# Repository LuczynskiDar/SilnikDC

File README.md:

# DC Engine driver ( Sterownik prędkości silnika DC )

> DC Engine driver is a [post graduate thesis](https://github.com/LuczynskiDar/SilnikDC/blob/master/Praca%20Podyplomowa%20-%20Sterownik%20Silnika%20-%20Dariusz%20%C5%81uczy%C5%84ski.pdf) done for AGH Univerisity of Science and Technology.

## Purpose of project

The purose of project was to use ECAD, EAGLE to design a circuit analog with
PCBA, then wirte a C program for Atmega32 to dirive a DC Enginge.

### Design approach

- For the project purposes will be used an mocro's internal clock,instead of using more reliable external crystal.
- Drivig the engine will be done on the basis of 4 switches, 2 for changing engine directions (Left/Right),
  which is actually changing micro's GPIO  and 2 responsible for incrementing and decrementing PWM signal.
- Interruption mechanism won't be used.
- I will use built in Fast PWM mechanism.
- The software will be done in C, usng Atmega Studio 7.
- The code will be debugged and uploaded thoreugh JTAG with MK7 Dragn programmer.
- Thce code will be validated with an eval board, Kamami ZL3.

### Block diagram

### Eagle ECAD designer

There are 2 Eagle project files:

- [Sterownik_DC.sch](https://github.com/LuczynskiDar/SilnikDC/blob/master/Sterownik_DC.sch) 
- [Sterownik_DC.brd](https://github.com/LuczynskiDar/SilnikDC/blob/master/Sterownik_DC.brd)

#### Schematic drawing

#### Material List (BOM)

#### Printed wiring board

#### PWB Drawing

### C Code

I created 2 files,

- [constants.h](https://github.com/LuczynskiDar/SilnikDC/blob/master/Sterownik_DC/constants.h), which contains definition for an internal clock flags,
- [sterownikdc.c](https://github.com/LuczynskiDar/SilnikDC/blob/master/Sterownik_DC/sterownikdc.c), which contains other methods along with main loop ```while(1)```.

### Design Verification

Code verificationn was performed on eval board, all 4 swithches were working properly.

- Set the dc engine to turn left, "l" on the display.

- Set the dc engine to turn right, "r" on te display.

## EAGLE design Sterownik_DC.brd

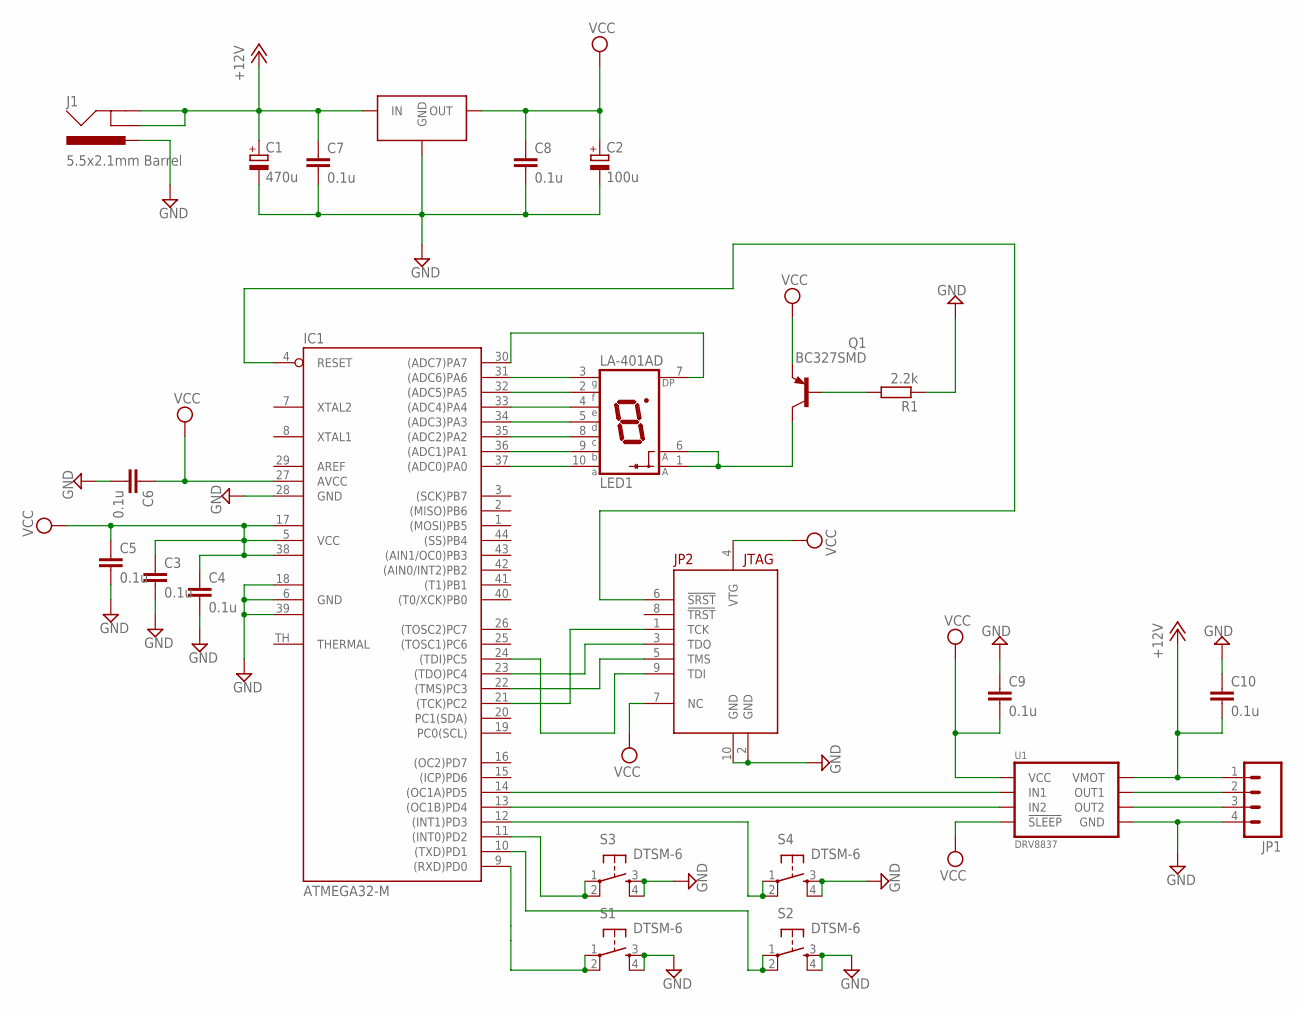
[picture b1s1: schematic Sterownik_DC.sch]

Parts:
C1: 470u; 175TMP-0810
C2: 100u; 175TMP-0810
C3, C4, C5, C6, C7, C8, C9, C10: 0.1u; C2012
IC1: ATMEGA32-M; MLF44-TH
J1: 5.5x2.1mm Barrel; POWER_JACK_SMD
JP1: M04SMD_STRAIGHT_COMBO; 1X04_SMD_STRAIGHT_COMBO
JP2: JTAGICE3-CONNECTOR50MIL-SMD; JTAGIC3-50MIL-SMD
LED1: LA-401AD; LA-401
Q1: BC327SMD; SOT23-BEC
R1: 2.2k; R2012
S1, S2, S3, S4: DTSM-6
U1: DRV8837; DSG
U$1: VREG-7805-DPAK2

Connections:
+12V: C1.+, C7.1, C10.2, J1.GND (GNDBREAK), J1.P$4 (GND), JP1.1, U1.1 (VMOT), U$1.VIN (IN)
GND: C1.-, C2.-, C3.2, C4.2, C5.2, C6.2, C7.2, C8.2, C9.1, C10.1, IC1.6 (GND), IC1.18 (GND1), IC1.28 (GND), IC1.39 (GND2), J1.VIN0 (PWR), JP1.4, JP2.2 (GND), JP2.10 (GND), R1.1, S1.3, S1.4, S2.3, S2.4, S3.3, S3.4, S4.3, S4.4, U1.4 (GND), U1.PAD (GND), U$1.GND
unnamed: JP1.2, U1.2 (OUT1)
unnamed: IC1.4 (RESET), JP2.6 (!SRST)
unnamed: IC1.35 ((ADC2)PA2), LED1.8 (C)
unnamed: Q1.B, R1.2
unnamed: IC1.11 ((INT0)PD2), S3.1, S3.2
unnamed: IC1.21 ((TCK)PC2), JP2.1 (TCK)
unnamed: IC1.23 ((TDO)PC4), JP2.3 (TDO)
unnamed: IC1.31 ((ADC6)PA6), LED1.3 (G)
unnamed: IC1.32 ((ADC5)PA5), LED1.2 (F)
unnamed: IC1.33 ((ADC4)PA4), LED1.4 (E)
unnamed: IC1.34 ((ADC3)PA3), LED1.5 (D)
unnamed: IC1.37 ((ADC0)PA0), LED1.10 (A)
unnamed: IC1.36 ((ADC1)PA1), LED1.9 (B)
unnamed: IC1.30 ((ADC7)PA7), LED1.7 (DP)
unnamed: LED1.1 (A), LED1.6 (A), Q1.C
unnamed: IC1.10 ((TXD)PD1), S2.1, S2.2
unnamed: IC1.22 ((TMS)PC3), JP2.5 (TMS)
unnamed: IC1.13 ((OC1B)PD4), U1.5 (IN2)
unnamed: IC1.12 ((INT1)PD3), S4.1, S4.2
unnamed: IC1.14 ((OC1A)PD5), U1.6 (IN1)
unnamed: IC1.9 ((RXD)PD0), S1.1, S1.2
unnamed: JP1.3, U1.3 (OUT2)
unnamed: IC1.24 ((TDI)PC5), JP2.9 (TDI)
VCC: C2.+, C3.1, C4.1, C5.1, C6.1, C8.1, C9.2, IC1.5 (VCC), IC1.17 (VCC1), IC1.27 (AVCC), IC1.38 (VCC2), JP2.4 (VTG), JP2.7 (NC), Q1.E, U1.7 (!SLEEP), U1.8 (VCC), U$1.VOUT (OUT)

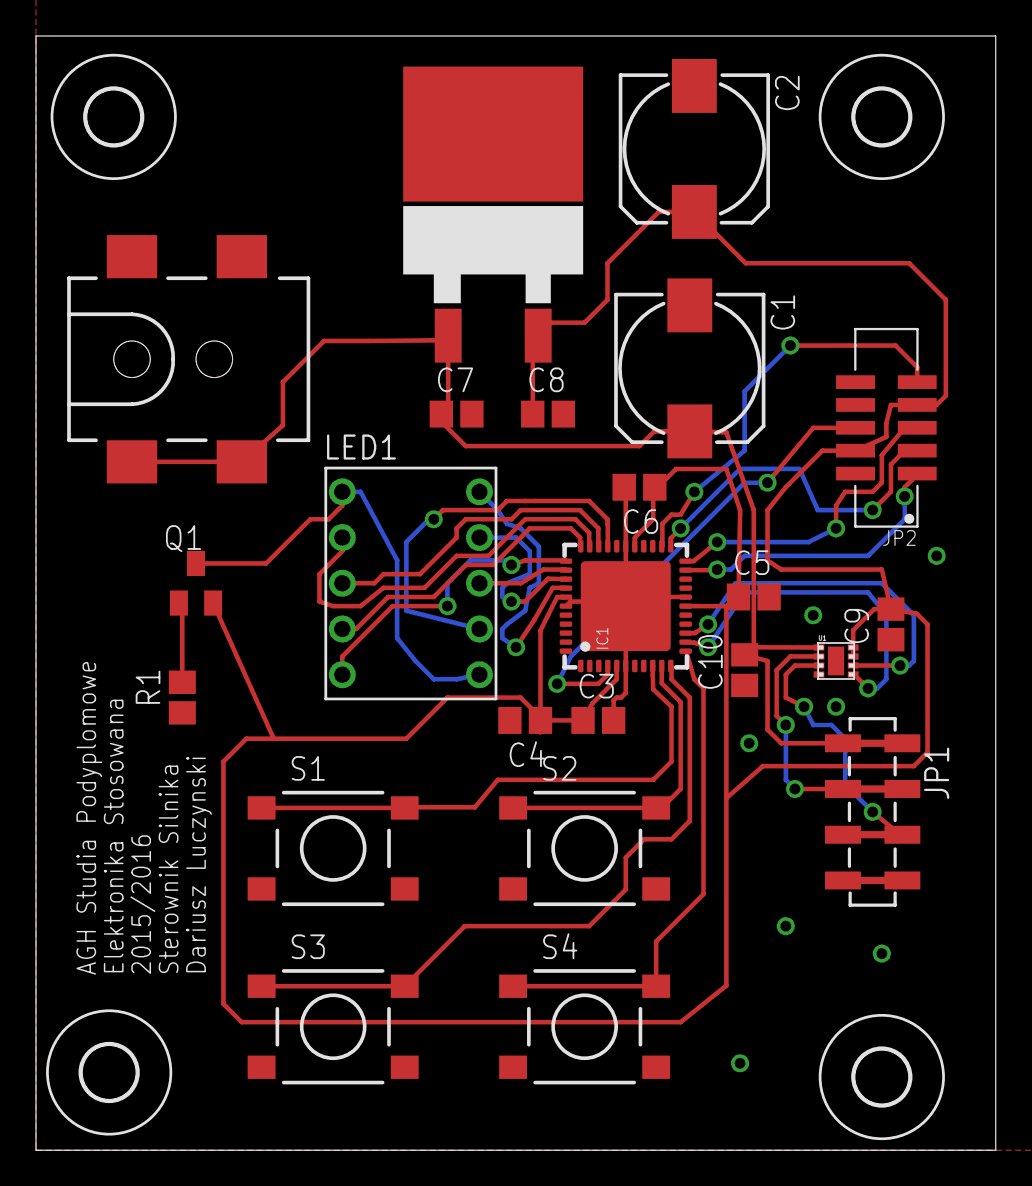
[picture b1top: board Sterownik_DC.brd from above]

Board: 2 copper layers, 53.3 x 61.9 mm, 28 parts (0 on the bottom side), 26 nets.

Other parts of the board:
U$2, U$3, U$4, U$5: 3,0
U$6: A4L-LOC

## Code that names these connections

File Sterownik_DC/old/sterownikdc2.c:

/*
 * Sterownik_DC.c
 *
 * Author : Dariusz Luczynski
 */ 



#include "constants.h"
#include <avr/pgmspace.h>
#include <stdlib.h>
#include <util/delay.h>
#include <avr/io.h>
#include <avr/interrupt.h>

//To set the two element LED  display
static const uint8_t PROGMEM DIRECTION[2]={0xC7, 0xAF};

// The direction indicator flag
static uint8_t dir_flag = 0xFF;

static uint8_t handler = 0;
// Direction flag indicator
volatile uint8_t pwm_flag=0xFF;

volatile uint8_t pwm_handler=102;

// Read pins indicator
volatile uint8_t pin_reader;

// Initialization of Timer1 for the PWM outputs
void timer1_initialize(void)
{

// To set the prescaler to divide the frequency per 1024
	TCCR1B |= (1<<CS12) | (1<<CS10); 
//  To set the Waveform Generator Mode to 8-bit Fast PWM
	TCCR1A |= (1<<WGM10);
	TCCR1B |= (1<<WGM12);
//  Set the PINs to zero, after the compare match event,
// when the minimum value is being reached 
	TCCR1A |= (1<<COM1A1) | (1<<COM1B1) ;	

// Set to the direction registers, PIN 4 and PIN5 
	DDRD |= (1<<PD4) | (1<<PD5);
	
//Initialize output compare registers
	OCR1A =	PWMDEF;
	OCR1B = PWMGND;	

}


//To chose from the tables a proper value for a proper LED display
//Inline do not recall the function just puts the code of the function there

void scan_key(void)
{
	uint8_t temp_dir = dir_flag;
	uint8_t temp_hand = handler;
	uint8_t temp_pwm = pwm_handler;
	
	uint8_t counter=0;
	if(counter==0)
	{
		pin_reader = ((~PIND) & 0x0F);
		// Set the column and calculate the key number
		if((pin_reader == 0x01) && ( (temp_dir & temp_hand) == 0))
		{
			temp_dir = 0xFF;
			temp_hand = 0x00;
		}
		else if((pin_reader ==0x02) && ( (dir_flag & temp_hand) == 0))
		{
			temp_dir = 0x00;
			temp_hand = 0xFF;
		}
		else if((pin_reader == 0x04) && ( temp_pwm > 0))
		{
			temp_pwm--;
			//temp_pwm-=10;
		}
		else if((pin_reader == 0x08) && ( temp_pwm < 255))
		{
			temp_pwm++;
			//temp_pwm+=10;
		}
		counter=100;
	} else counter--;
	
	dir_flag = temp_dir;
	handler = temp_hand;
	pwm_handler = temp_pwm;
}

void pwm_set(void)
{
	//OCR1A = 255;
	if (pwm_flag == 0xff) OCR1A = pwm_handler;
	if (pwm_flag == 0x00) OCR1B = pwm_handler;
}

void show_direction( void)

{
	uint8_t temp = 0xFF;
	uint8_t pwm_holder;
	PORTA = 0xFF;
	if(dir_flag == 0xFF)
	{
		temp = pgm_read_byte(&DIRECTION[0]);

		pwm_holder = OCR1A;
		/*
		 PORTA |= (1<<PA3);   //ustaw bit PA3
		 PORTA &= ~(1<<PA2);   //zeruj bit PA2
		 */
		//DDRD = (0<<PD4);
		DDRD &= ~(1<<PD4);
		DDRD = (1<<PD5);
		OCR1B = pwm_holder;
		pwm_flag = 0xFF;
	}
	if(dir_flag == 0x00)
	{
		temp = pgm_read_byte(&DIRECTION[1]);
		//temp = pgm_read_byte(&DIRECTIONR[number]);
		pwm_holder = OCR1B;
		//DDRD = (0<<PD5);
		DDRD &= ~(1<<PD5);
		DDRD = (1<<PD4);
		OCR1A = pwm_holder;
		pwm_flag = 0x00;
	}
	PORTA = temp;
}


int main(void)
{
    timer1_initialize();
	DDRA = 0xFF;
	PORTD |= 0x0F;
    while (1) 

    {
		scan_key();
		show_direction();
		pwm_set();
		_delay_ms(10);
    }
}

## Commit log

2016-07-15 Add files via upload
    First commit
2019-01-04 images
2019-01-04 diagram
2019-01-04 md updates
2019-01-04 thesis
2019-01-04 ecad
2019-01-04 design approach
2019-01-05 design approahces
2019-01-05 bom image
2019-01-05 add c code
2019-01-05 description

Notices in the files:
parts and their libraries:
SparkFun-Connectors: Licensing: CC v3.0 Share-Alike You are welcome to use this library for commercial purposes.
